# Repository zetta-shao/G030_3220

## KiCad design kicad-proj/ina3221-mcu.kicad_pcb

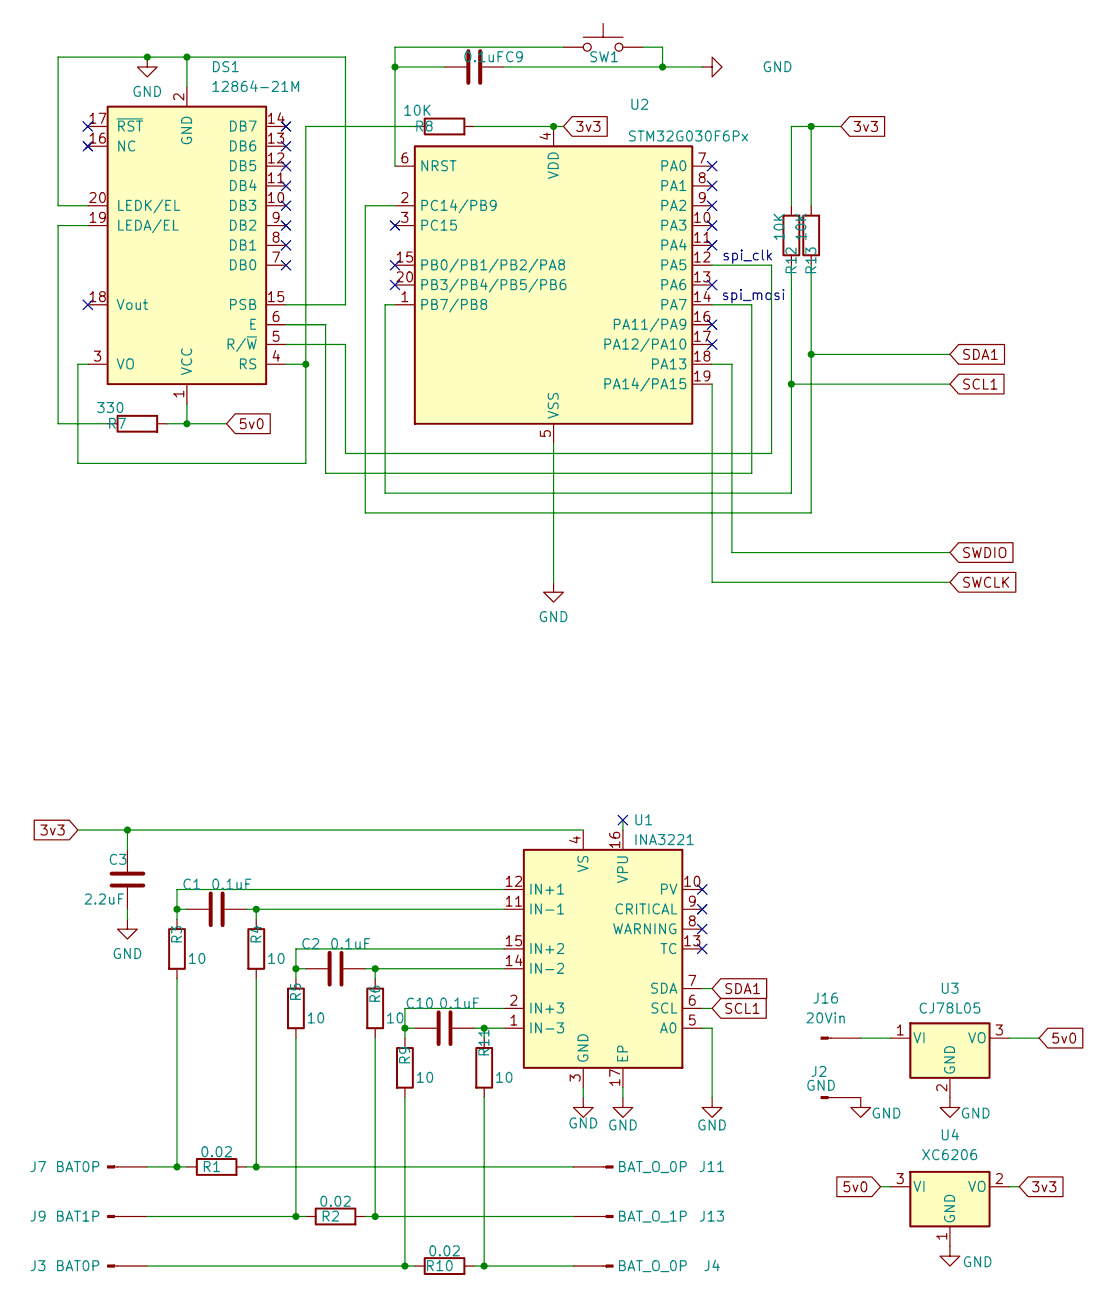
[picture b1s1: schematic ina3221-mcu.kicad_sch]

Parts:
C1, C2, C9, C10: 0.1uF; C_0603_1608Metric_Pad1.08x0.95mm_HandSolder
C3: 2.2uF; C_0603_1608Metric_Pad1.08x0.95mm_HandSolder
DS1: 12864-21M; AG12864E
J2: GND; SolderWire-0.127sqmm_1x01_D0.48mm_OD1mm
J3, J7: BAT0P; SolderWire-0.127sqmm_1x01_D0.48mm_OD1mm
J4, J11: BAT_O_0P; SolderWire-0.127sqmm_1x01_D0.48mm_OD1mm
J9: BAT1P; SolderWire-0.127sqmm_1x01_D0.48mm_OD1mm
J13: BAT_O_1P; SolderWire-0.127sqmm_1x01_D0.48mm_OD1mm
J16: 20Vin; SolderWire-0.127sqmm_1x01_D0.48mm_OD1mm
R1, R2, R10: 0.02; R_1206_3216Metric_Pad1.30x1.75mm_HandSolder
R3, R4, R5, R6, R9, R11: 10; R_0603_1608Metric_Pad0.98x0.95mm_HandSolder
R7: 330; R_0603_1608Metric_Pad0.98x0.95mm_HandSolder
R8, R12, R13: 10K; R_0603_1608Metric_Pad0.98x0.95mm_HandSolder
SW1: SW_Push; SW_SPST_TL3305A
U1: INA3221; QFN-16-1EP_4x4mm_P0.65mm_EP2.1x2.1mm
U2: STM32G030F6Px; TSSOP-20_4.4x6.5mm_P0.65mm
U3: CJ78L05; SOT-89-3
U4: XC6206; SOT-23

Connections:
3v3: C3.1, R8.2, R12.2, R13.2, U1.4 (VS), U2.4 (VDD), U4.2 (VO)
5v0: DS1.1 (VCC), R7.2, U3.3 (VO), U4.3 (VI)
GND: C3.2, C9.1, DS1.2 (GND), DS1.15 (PSB), DS1.20 (LEDK/EL), J2.1, SW1.2, U1.3 (GND), U1.5 (A0), U1.17 (EP), U2.5 (VSS), U3.2 (GND), U4.1 (GND)
unnamed: DS1.6 (E), U2.14 (PA7)
unnamed: DS1.19 (LEDA/EL), R7.1
unnamed: DS1.3 (VO), DS1.4 (RS), R8.1
unnamed: DS1.5 (R/~W), U2.12 (PA5)
unnamed: J3.1, R9.2, R10.1
unnamed: J4.1, R10.2, R11.2
unnamed: J7.1, R1.1, R3.2
unnamed: J9.1, R2.1, R5.2
unnamed: J11.1, R1.2, R4.2
unnamed: J13.1, R2.2, R6.2
unnamed: J16.1, U3.1 (VI)
unnamed: C1.1, R3.1, U1.12 (IN+1)
unnamed: C2.1, R5.1, U1.15 (IN+2)
unnamed: C10.1, R9.1, U1.2 (IN+3)
unnamed: C1.2, R4.1, U1.11 (IN-1)
unnamed: C2.2, R6.1, U1.14 (IN-2)
unnamed: C10.2, R11.1, U1.1 (IN-3)
unnamed: C9.2, SW1.1, U2.6 (NRST)
SCL1: R12.1, U1.6 (SCL), U2.1 (PB7/PB8)
SDA1: R13.1, U1.7 (SDA), U2.2 (PC14/PB9)
SWCLK: U2.19 (PA14/PA15)
SWDIO: U2.18 (PA13)

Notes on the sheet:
spi_clk
spi_mosi

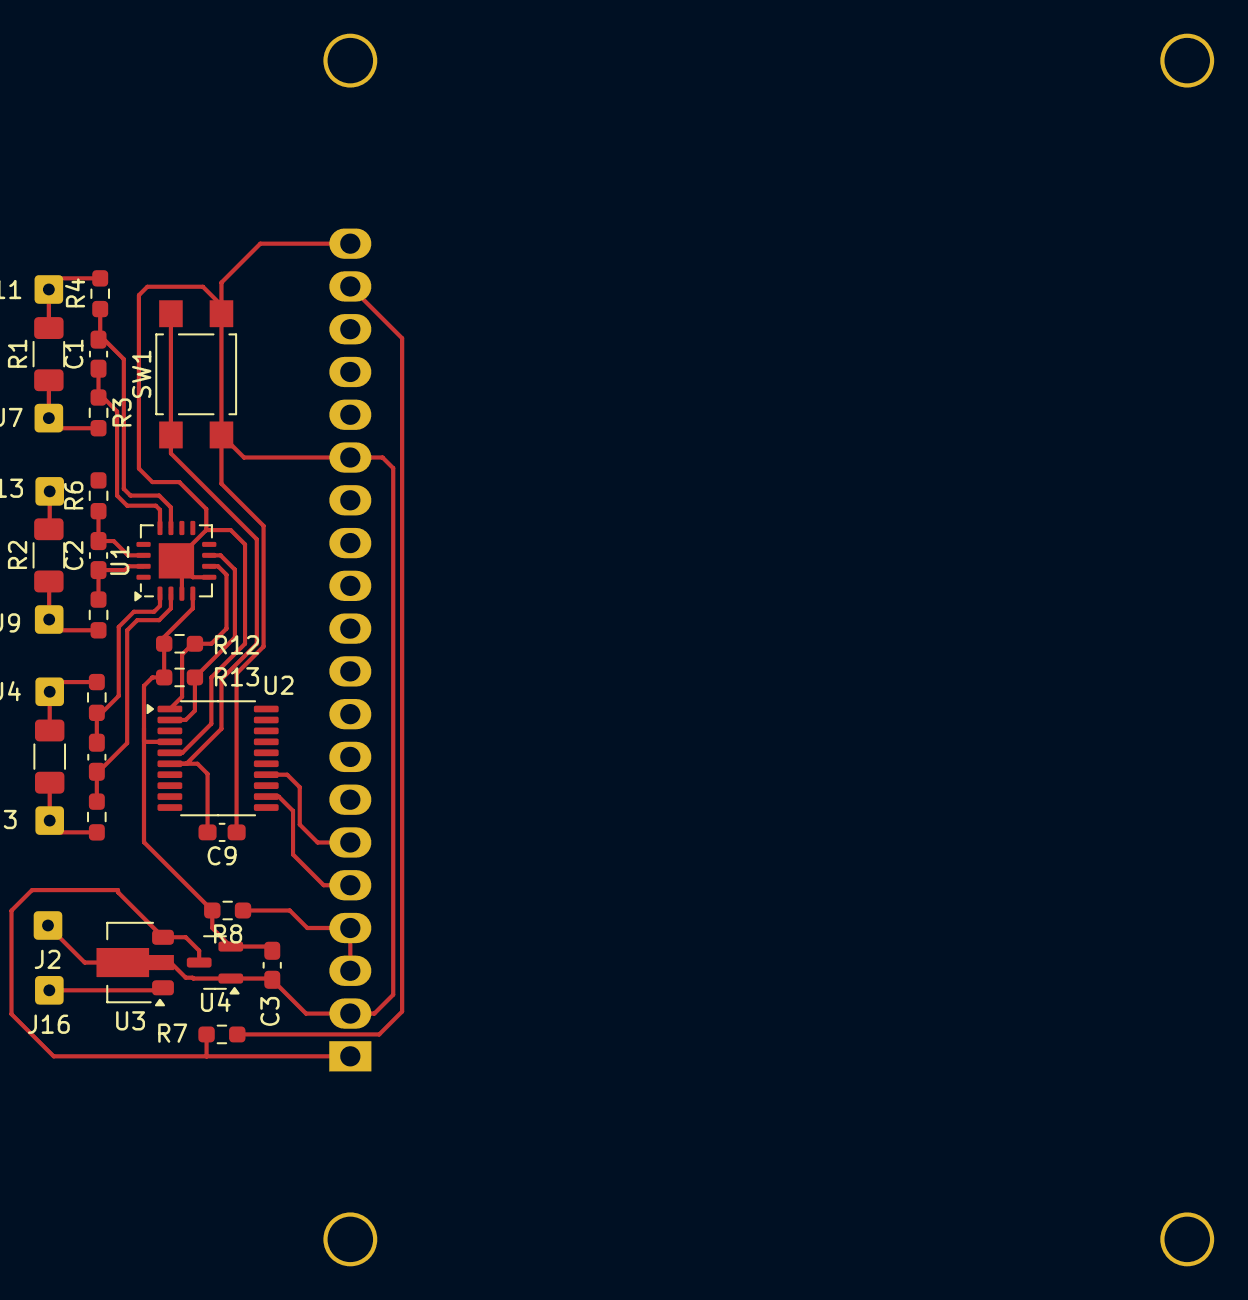
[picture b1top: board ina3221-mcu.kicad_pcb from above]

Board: 2 copper layers, 32 parts (1 on the bottom side), 23 nets.

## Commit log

2024-09-03 change project name to G030_3220
2024-09-03 add st7920 spi_mode3
2024-09-19 first release
2024-10-01 update ssd1306 code for sh1106 132x64 OLED display
2024-10-04 add i2c irq mode, change ina3221 to i2c2
2024-10-08 unity gpio_t name.
2025-09-11 change to common lib.
